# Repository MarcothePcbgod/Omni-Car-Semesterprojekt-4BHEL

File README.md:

# Omni-Car-Semesterprojekt-4BHEL
Backup für KiCad

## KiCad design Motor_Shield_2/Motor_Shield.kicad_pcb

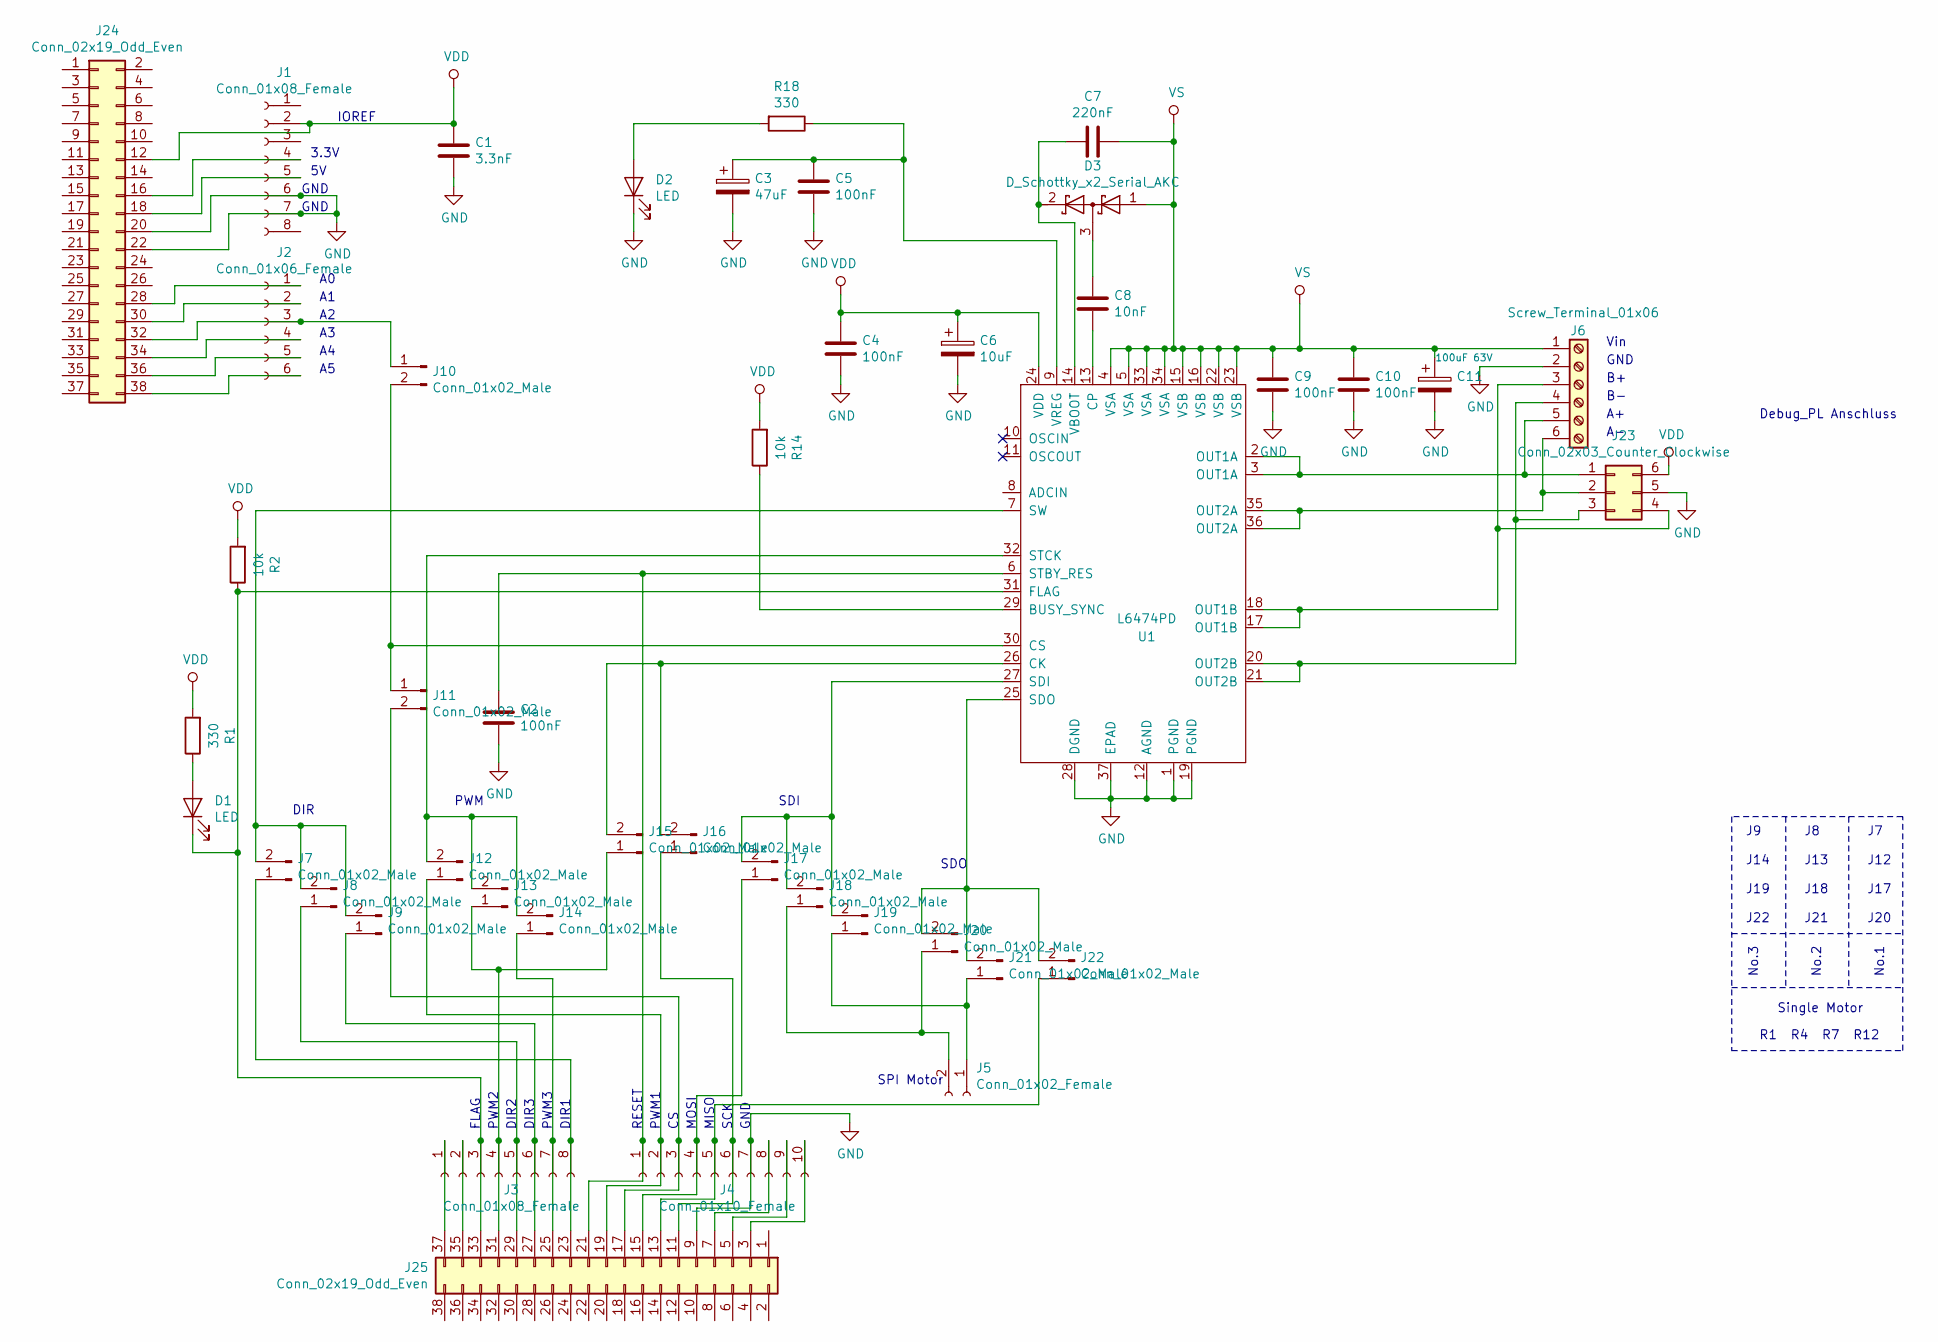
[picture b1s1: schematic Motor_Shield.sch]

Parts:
C1: 3.3nF; C_1206_3216Metric_Pad1.42x1.75mm_HandSolder
C2, C4, C5, C9, C10: 100nF; C_1206_3216Metric_Pad1.42x1.75mm_HandSolder
C3: 47uF; CP_EIA-3528-12_Kemet-T_Pad1.50x2.35mm_HandSolder
C6: 10uF; CP_EIA-3528-12_Kemet-T_Pad1.50x2.35mm_HandSolder
C7: 220nF; C_1206_3216Metric_Pad1.42x1.75mm_HandSolder
C8: 10nF; C_1206_3216Metric_Pad1.42x1.75mm_HandSolder
C11: 100uF 63V; C_Radial_D10.0mm_H20.0mm_P5.00mm
D1, D2: LED; D_1206_3216Metric_Pad1.42x1.75mm_HandSolder
D3: D_Schottky_x2_Serial_AKC; SC-59_Handsoldering
J1, J3: Conn_01x08_Female; PinSocket_1x08_P2.54mm_Vertical
J2: Conn_01x06_Female; PinSocket_1x06_P2.54mm_Vertical
J4: Conn_01x10_Female; PinSocket_1x10_P2.54mm_Vertical
J5: Conn_01x02_Female; PinSocket_1x02_P2.54mm_Vertical
J6: Screw_Terminal_01x06; TerminalBlock_bornier-6_P5.08mm
J7, J8, J9, J10, J11, J12, J13, J14, J15, J16, J17, J18, J19, J20, J21, J22: Conn_01x02_Male; PinHeader_1x02_P2.54mm_Vertical
J23: Conn_02x03_Counter_Clockwise; PinHeader_2x03_P2.54mm_Vertical
J24, J25: Conn_02x19_Odd_Even; PinHeader_2x19_P2.54mm_Vertical
R1, R18: 330; R_1206_3216Metric_Pad1.42x1.75mm_HandSolder
R2, R14: 10k; R_1206_3216Metric_Pad1.42x1.75mm_HandSolder
U1: L6474PD; ST_PowerSSO-36_SlugDown_ThermalVias

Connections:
GND: C1.2, C2.2, C3.2, C4.2, C5.2, C6.2, C9.2, C10.2, C11.2, D2.1 (K), J1.6, J1.7, J4.7, J6.2, J23.5, J24.20, J24.22, J25.9, U1.1 (PGND), U1.12 (AGND), U1.19 (PGND), U1.28 (DGND), U1.37 (EPAD)
unnamed: C2.1, J4.1, J25.21, U1.6 (STBY_RES)
unnamed: C3.1, C5.1, R18.1, U1.9 (VREG)
unnamed: C7.2, D3.2 (K), U1.14 (VBOOT)
unnamed: C8.1, D3.3 (common)
unnamed: C8.2, U1.13 (CP)
unnamed: D1.1 (K), J3.3, J25.33, R2.1, U1.31 (FLAG)
unnamed: D1.2 (A), R1.1
unnamed: D2.2 (A), R18.2
unnamed: J1.4, J24.16
unnamed: J1.5, J24.18
unnamed: J2.1, J24.28
unnamed: J2.2, J24.30
unnamed: J2.4, J24.34
unnamed: J2.5, J24.36
unnamed: J2.6, J24.38
unnamed: J7.2, J8.2, J9.2, U1.7 (SW)
unnamed: J2.3, J10.1, J24.32
unnamed: J10.2, J11.1, U1.30 (CS)
unnamed: J4.3, J11.2, J25.17
unnamed: J4.2, J12.1, J25.19
unnamed: J12.2, J13.2, J14.2, U1.32 (STCK)
unnamed: J3.4, J13.1, J15.1, J25.31
unnamed: J3.7, J14.1, J25.25
unnamed: J15.2, J16.2, U1.26 (CK)
unnamed: J4.6, J16.1, J25.11
unnamed: J4.4, J17.1, J25.15
unnamed: J17.2, J18.2, J19.2, U1.27 (SDI)
unnamed: J5.2, J18.1, J20.1
unnamed: J5.1, J19.1, J21.1
unnamed: J20.2, J21.2, J22.2, U1.25 (SDO)
unnamed: J4.5, J22.1, J25.13
unnamed: J6.5, J23.1, U1.2 (OUT1A), U1.3 (OUT1A)
unnamed: J6.6, J23.2, U1.35 (OUT2A), U1.36 (OUT2A)
unnamed: J6.4, J23.3, U1.20 (OUT2B), U1.21 (OUT2B)
unnamed: J6.3, J23.4, U1.17 (OUT1B), U1.18 (OUT1B)
unnamed: J4.10, J25.3
unnamed: J4.9, J25.5
unnamed: J4.8, J25.7
unnamed: J3.8, J7.1, J25.23
unnamed: J3.6, J9.1, J25.27
unnamed: J3.5, J8.1, J25.29
unnamed: J3.2, J25.35
unnamed: J3.1, J25.37
unnamed: R14.1, U1.29 (BUSY_SYNC)
VDD: C1.1, C4.1, C6.1, J1.2, J23.6, J24.12, R1.2, R2.2, R14.2, U1.24 (VDD)
VS: C7.1, C9.1, C10.1, C11.1, D3.1 (A), J6.1, U1.4 (VSA), U1.5 (VSA), U1.15 (VSB), U1.16 (VSB), U1.22 (VSB), U1.23 (VSB), U1.33 (VSA), U1.34 (VSA)

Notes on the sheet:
DIR
PWM
SDI
SDO
SPI Motor
No.3
No.2
No.1
Single Motor
R1 R4 R7 R12
Vin
GND
IOREF
3.3V
FLAG
PWM2
DIR2
DIR3
PWM3
DIR1
RESET
PWM1
MOSI
MISO
SCK
Debug_PL Anschluss
J7 J12 J17 J20
J8 J13 J18 J21
J9 J14 J19 J22

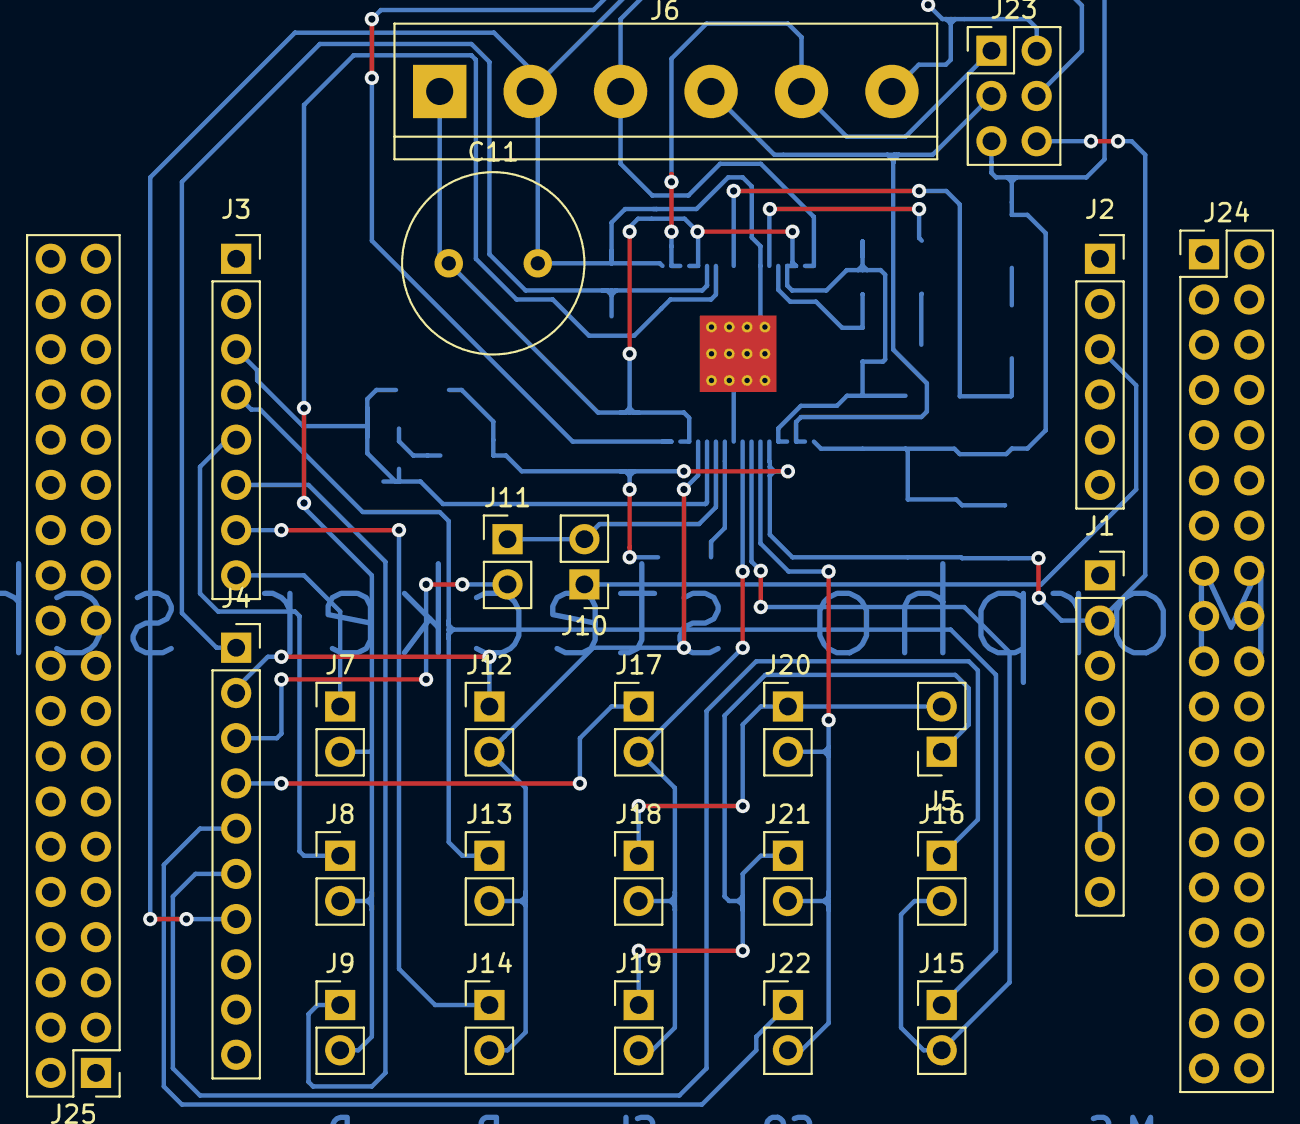
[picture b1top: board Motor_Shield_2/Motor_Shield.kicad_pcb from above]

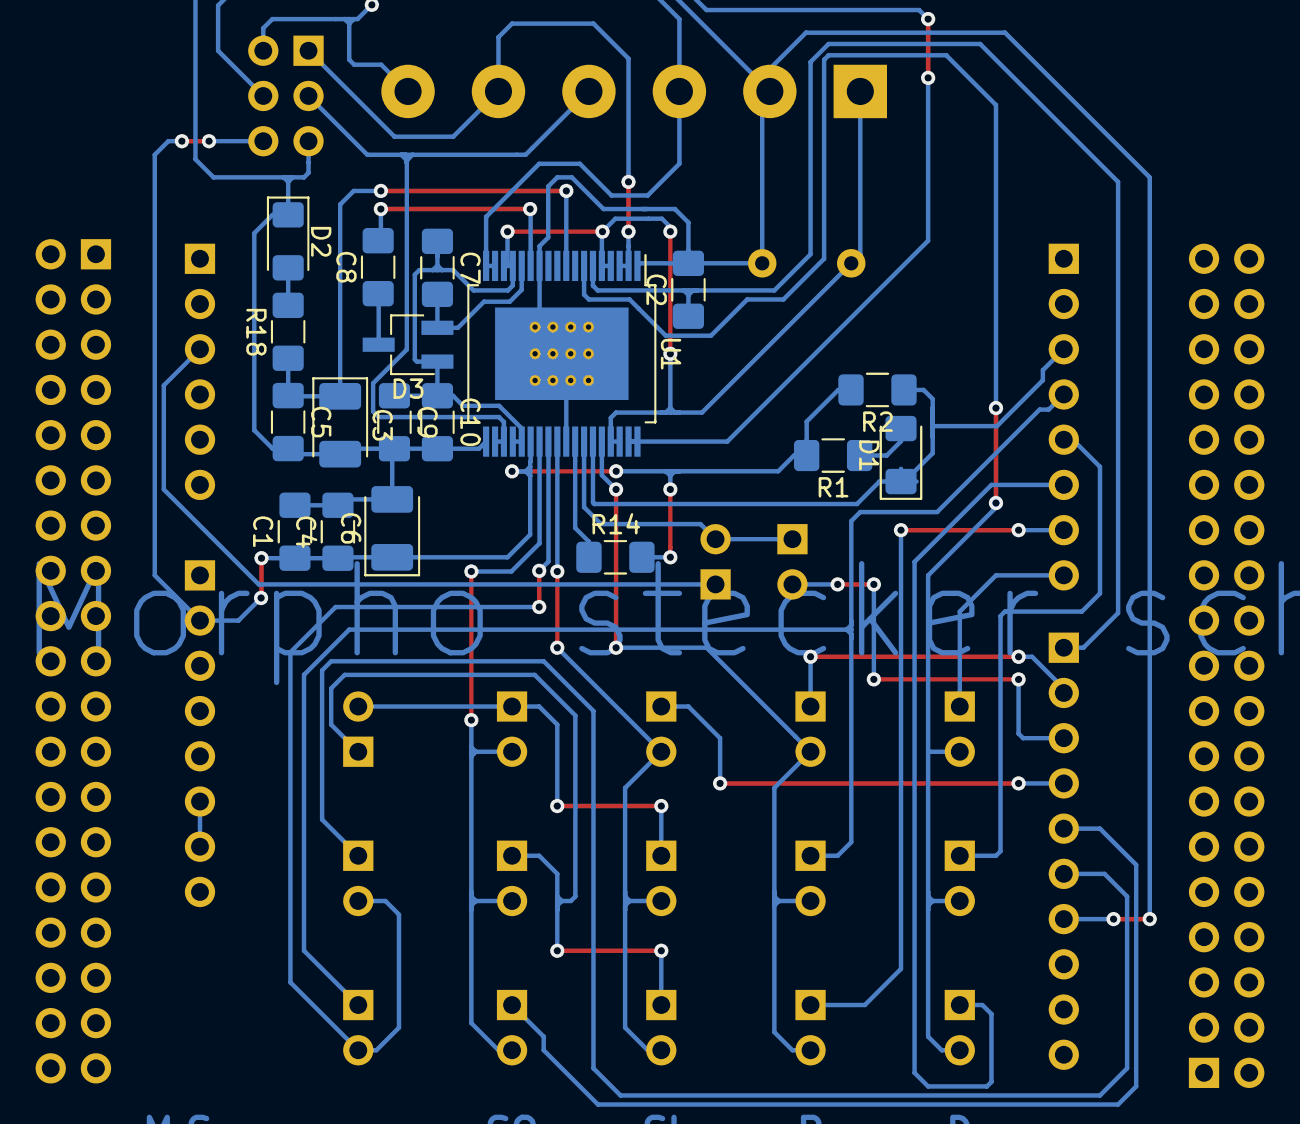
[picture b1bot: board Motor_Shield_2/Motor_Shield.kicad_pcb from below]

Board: 2 copper layers, 44 parts (18 on the bottom side), 47 nets.

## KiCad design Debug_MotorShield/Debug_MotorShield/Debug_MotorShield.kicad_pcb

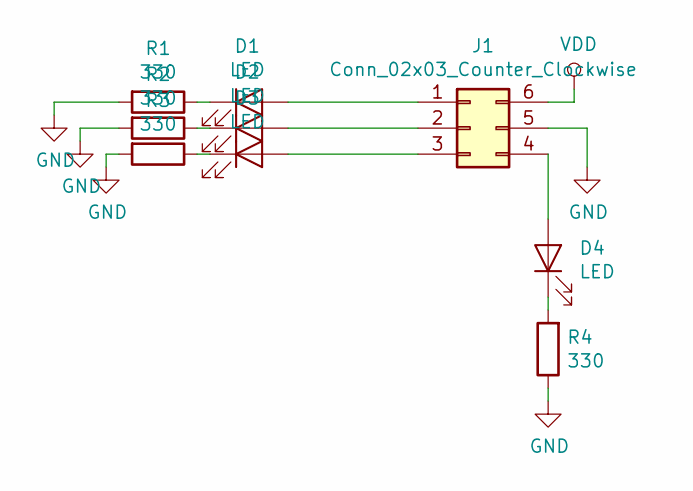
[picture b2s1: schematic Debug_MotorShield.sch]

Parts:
D1, D2, D3, D4: LED; LED_1206_3216Metric_Pad1.42x1.75mm_HandSolder
J1: Conn_02x03_Counter_Clockwise; PinHeader_2x03_P2.54mm_Vertical
R1, R2, R3, R4: 330; R_1206_3216Metric_Pad1.42x1.75mm_HandSolder

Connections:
GND: J1.5, R1.2, R2.2, R3.2, R4.1
unnamed: D1.1 (K), R1.1
unnamed: D1.2 (A), J1.1
unnamed: D2.1 (K), R2.1
unnamed: D2.2 (A), J1.2
unnamed: D3.1 (K), R3.1
unnamed: D3.2 (A), J1.3
unnamed: D4.1 (K), R4.2
unnamed: D4.2 (A), J1.4
VDD: J1.6

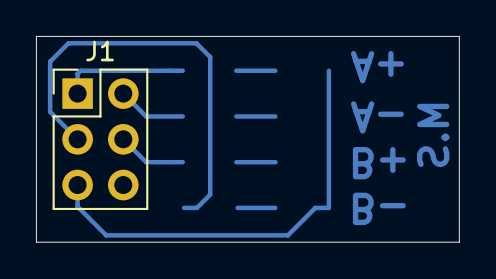
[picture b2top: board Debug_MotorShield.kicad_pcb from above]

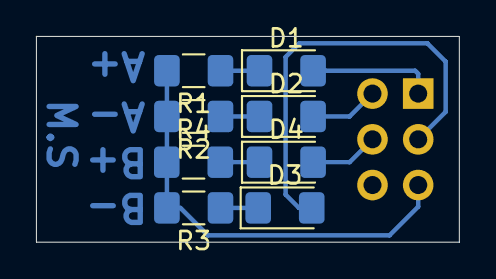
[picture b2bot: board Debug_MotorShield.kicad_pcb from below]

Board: 2 copper layers, 23.5 x 11.4 mm, 9 parts (8 on the bottom side), 9 nets.

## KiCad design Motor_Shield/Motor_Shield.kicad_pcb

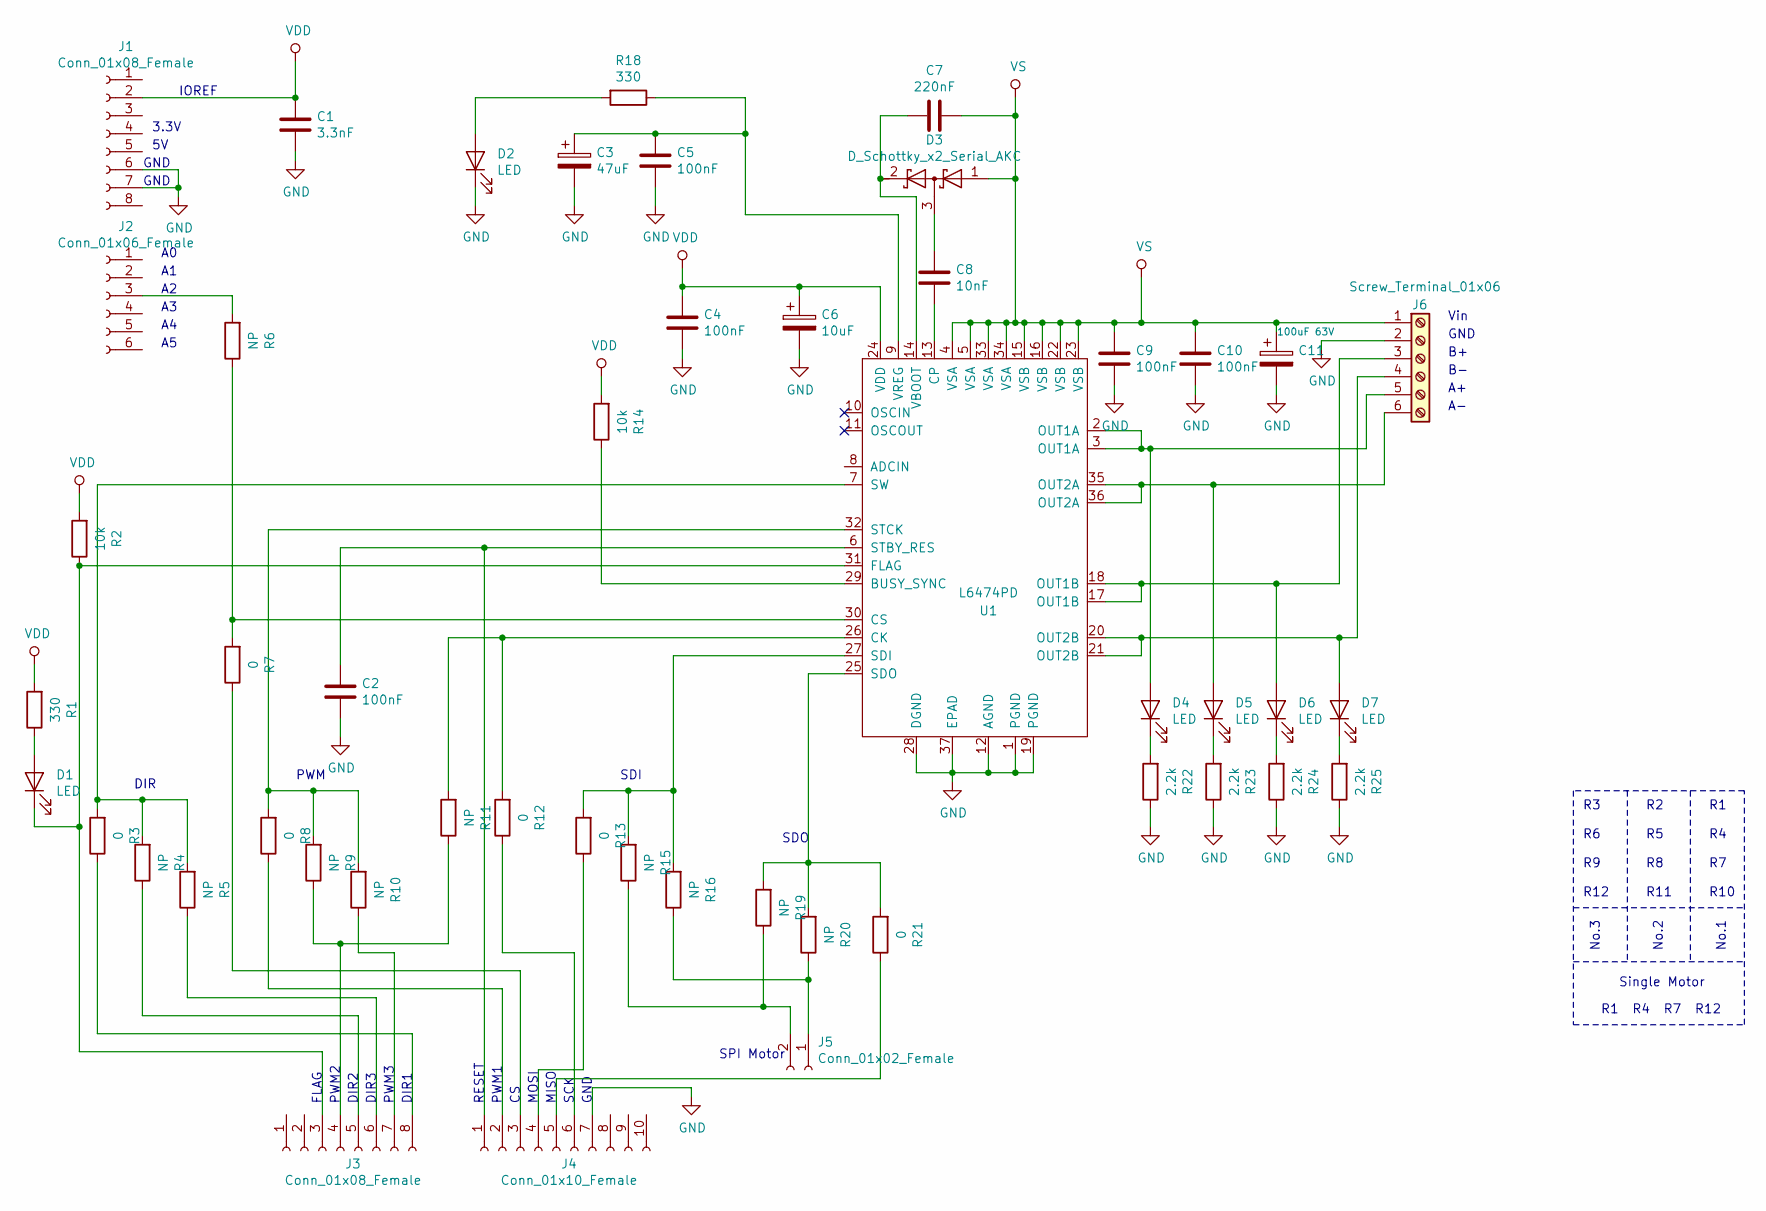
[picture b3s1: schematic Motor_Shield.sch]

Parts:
C1: 3.3nF; C_1206_3216Metric_Pad1.42x1.75mm_HandSolder
C2, C4, C5, C9, C10: 100nF; C_1206_3216Metric_Pad1.42x1.75mm_HandSolder
C3: 47uF; CP_EIA-3528-12_Kemet-T_Pad1.50x2.35mm_HandSolder
C6: 10uF; CP_EIA-3528-12_Kemet-T_Pad1.50x2.35mm_HandSolder
C7: 220nF; C_1206_3216Metric_Pad1.42x1.75mm_HandSolder
C8: 10nF; C_1206_3216Metric_Pad1.42x1.75mm_HandSolder
C11: 100uF 63V; C_Radial_D10.0mm_H20.0mm_P5.00mm
D1, D2: LED; D_1206_3216Metric_Pad1.42x1.75mm_HandSolder
D3: D_Schottky_x2_Serial_AKC; SC-59_Handsoldering
D4, D5, D6, D7: LED; D_1206_3216Metric
J1, J3: Conn_01x08_Female; PinSocket_1x08_P2.54mm_Vertical
J2: Conn_01x06_Female; PinSocket_1x06_P2.54mm_Vertical
J4: Conn_01x10_Female; PinSocket_1x10_P2.54mm_Vertical
J5: Conn_01x02_Female; PinSocket_1x02_P2.54mm_Vertical
J6: Screw_Terminal_01x06; TerminalBlock_bornier-6_P5.08mm
R1, R18: 330; R_1206_3216Metric_Pad1.42x1.75mm_HandSolder
R2, R14: 10k; R_1206_3216Metric_Pad1.42x1.75mm_HandSolder
R3, R7, R8, R12, R13, R21: 0; R_1206_3216Metric_Pad1.42x1.75mm_HandSolder
R4, R5, R6, R9, R10, R11, R15, R16, R19, R20: NP; R_1206_3216Metric_Pad1.42x1.75mm_HandSolder
R22, R23, R24, R25: 2.2k; R_1206_3216Metric_Pad1.42x1.75mm_HandSolder
U1: L6474PD; ST_PowerSSO-36_SlugDown_ThermalVias

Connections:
GND: C1.2, C2.2, C3.2, C4.2, C5.2, C6.2, C9.2, C10.2, C11.2, D2.1 (K), J1.6, J1.7, J4.7, J6.2, R22.1, R23.1, R24.1, R25.1, U1.1 (PGND), U1.12 (AGND), U1.19 (PGND), U1.28 (DGND), U1.37 (EPAD)
unnamed: C2.1, J4.1, U1.6 (STBY_RES)
unnamed: C3.1, C5.1, R18.1, U1.9 (VREG)
unnamed: C7.2, D3.2 (K), U1.14 (VBOOT)
unnamed: C8.1, D3.3 (common)
unnamed: C8.2, U1.13 (CP)
unnamed: D1.1 (K), J3.3, R2.1, U1.31 (FLAG)
unnamed: D1.2 (A), R1.1
unnamed: D2.2 (A), R18.2
unnamed: D4.1 (K), R22.2
unnamed: D4.2 (A), J6.5, U1.2 (OUT1A), U1.3 (OUT1A)
unnamed: D5.1 (K), R23.2
unnamed: D5.2 (A), J6.6, U1.35 (OUT2A), U1.36 (OUT2A)
unnamed: D6.1 (K), R24.2
unnamed: D6.2 (A), J6.3, U1.17 (OUT1B), U1.18 (OUT1B)
unnamed: D7.1 (K), R25.2
unnamed: D7.2 (A), J6.4, U1.20 (OUT2B), U1.21 (OUT2B)
unnamed: J2.3, R6.2
unnamed: J3.4, R9.1, R11.1
unnamed: J3.5, R4.1
unnamed: J3.6, R5.1
unnamed: J3.7, R10.1
unnamed: J3.8, R3.1
unnamed: J4.2, R8.1
unnamed: J4.3, R7.1
unnamed: J4.4, R13.1
unnamed: J4.5, R21.1
unnamed: J4.6, R12.1
unnamed: J5.1, R16.1, R20.1
unnamed: J5.2, R15.1, R19.1
unnamed: R3.2, R4.2, R5.2, U1.7 (SW)
unnamed: R6.1, R7.2, U1.30 (CS)
unnamed: R8.2, R9.2, R10.2, U1.32 (STCK)
unnamed: R11.2, R12.2, U1.26 (CK)
unnamed: R13.2, R15.2, R16.2, U1.27 (SDI)
unnamed: R14.1, U1.29 (BUSY_SYNC)
unnamed: R19.2, R20.2, R21.2, U1.25 (SDO)
VDD: C1.1, C4.1, C6.1, J1.2, R1.2, R2.2, R14.2, U1.24 (VDD)
VS: C7.1, C9.1, C10.1, C11.1, D3.1 (A), J6.1, U1.4 (VSA), U1.5 (VSA), U1.15 (VSB), U1.16 (VSB), U1.22 (VSB), U1.23 (VSB), U1.33 (VSA), U1.34 (VSA)

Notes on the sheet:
DIR
PWM
SDI
SDO
SPI Motor
R3 R6 R9 R12
R2 R5 R8 R11
R1 R4 R7 R10
No.3
No.2
No.1
Single Motor
R1 R4 R7 R12
Vin
GND
IOREF
3.3V
FLAG
PWM2
DIR2
DIR3
PWM3
DIR1
RESET
PWM1
MOSI
MISO
SCK

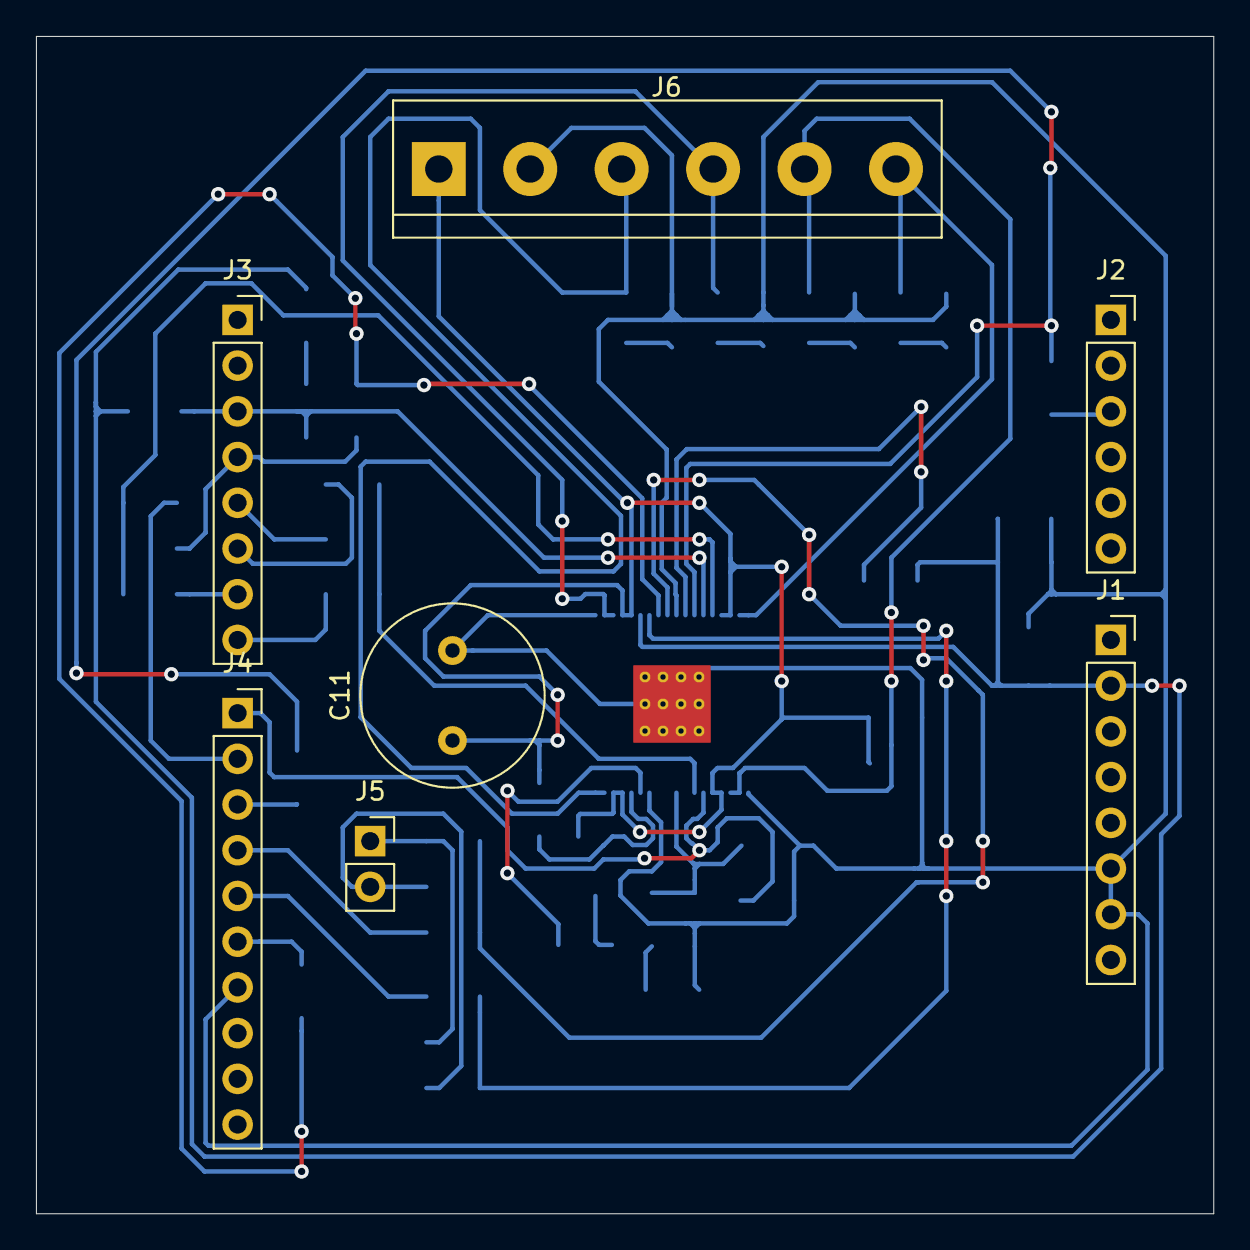
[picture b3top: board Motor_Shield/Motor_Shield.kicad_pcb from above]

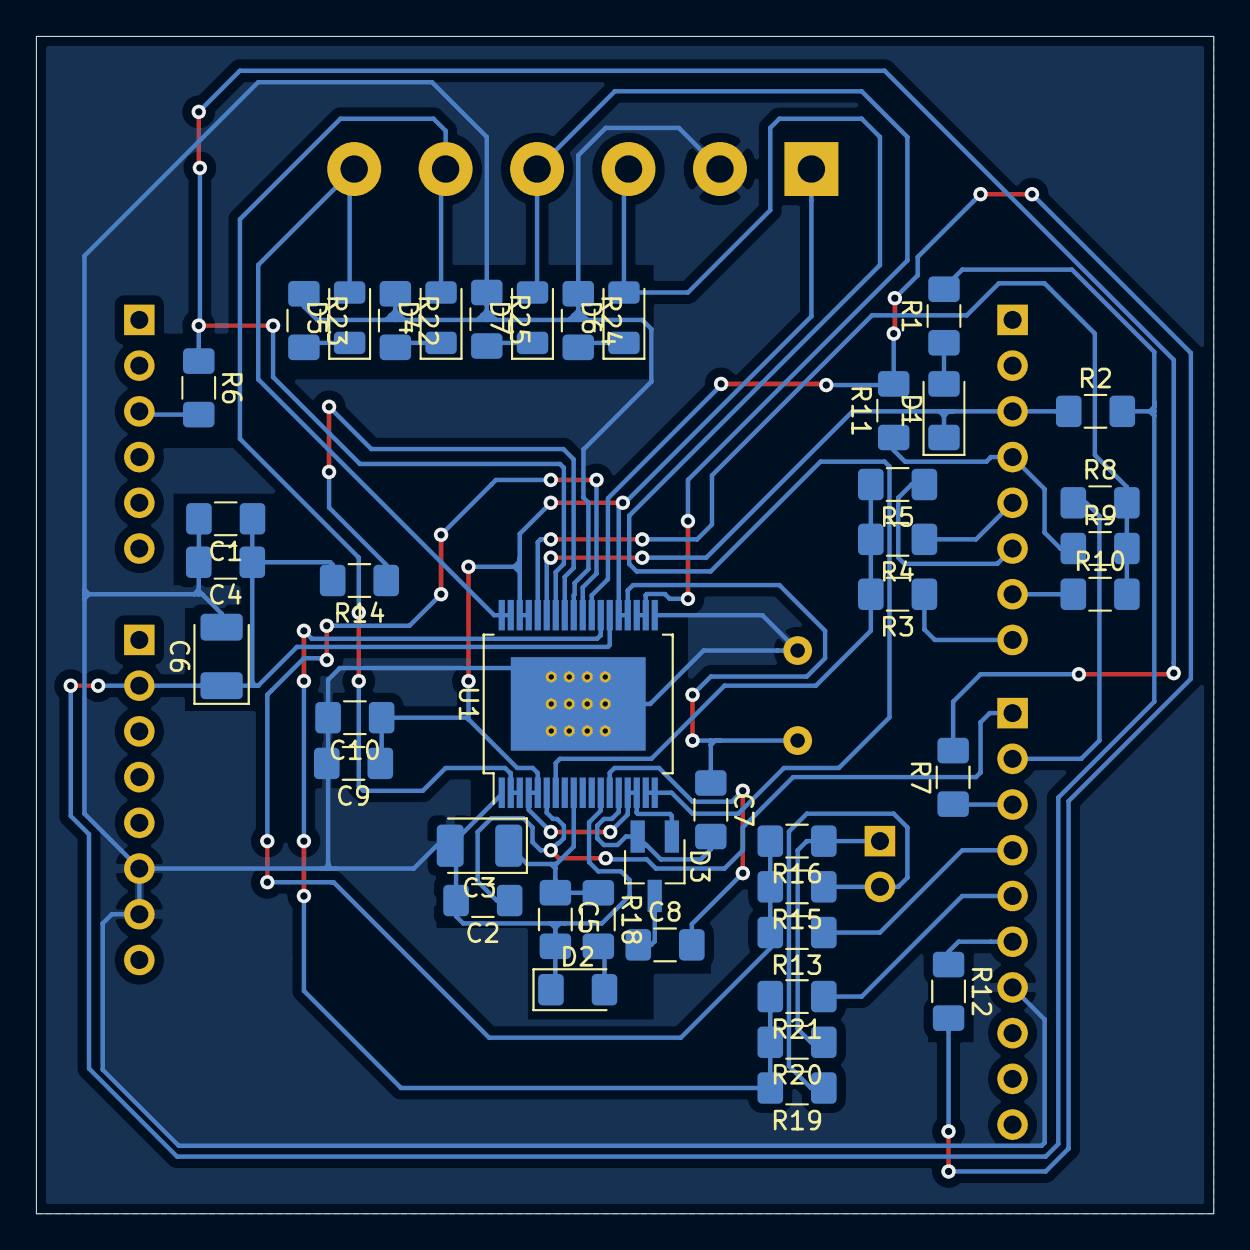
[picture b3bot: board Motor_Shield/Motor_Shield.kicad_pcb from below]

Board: 2 copper layers, 65.4 x 65.4 mm, 49 parts (42 on the bottom side), 39 nets.

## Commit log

2020-01-24 Erste Basis für AP und Datenübertragung
2020-01-24 Mögliche Bewegungen eingefügt
2020-01-25 Grid Def fehlt
2020-01-25 Array in HEX geändert
2020-01-25 Buttons richtig platziert
2020-01-26 Buttons entfernt und auf Keybindevents gendert
    N
2020-01-26 Buttons entfernt und auf Keybindevents geändert
    Nächster Schritt Darstellung von "Fakebuttons" mit Drückanimation
2020-01-27 TEST
2020-01-27 Buttonanimation hinzugefügt Optik fehlt
2020-01-27 Button sind jetzt Pfeile
2020-01-27 Ladebalken hinzugefügt
2020-01-28 Unnötige Buttons entfernt
2020-01-28 Unnötige Taskrequests wurden entfernt UNGETESTET
2020-01-28 Mögliche Funktion für Akkustatus
    Akkustatus Update ist drinnen aber nicht getestet weil send func im .ino file fehlt
2020-01-29 Auslesen der Webseite fertig verarbeitung fehlt
2020-01-29 Akkustand Req hinzugefügt
2020-01-29 Daten convert fertig
2020-01-31 PopUp-Fenster erstellt falls keine Verbindung
2020-02-02 First Blink Test
2020-02-16 Verbindungsbestätigung hinzugefügt
2020-02-17 swaped 57 with 58
2020-02-17 Zurück geswaped
2020-02-17 Error gefixed
2020-02-17 Pfade geupdated
2020-02-27 PCB angefangen
2020-02-28 UART Komm implementiert
2020-02-28 UART implementiert im INT-Mode
2020-02-28 Pcb fertig aber noch nicht optimal
2020-03-01 Version mit Pin Header statt SMD R
2020-03-02 pcb 70% fertig
2020-03-02 Fertig
2020-03-03 Überarbeiten das Pin Header schlecht plaziert waren
2020-03-03 PCB fertig
2020-03-03 Debug MotorShield fertig
2020-03-06 Morpho_Header hinzugefügt pcb fehlt aber noch
2020-06-13 mainC für Levelansteuerung
2020-06-13 Endbedinung hinzugefügt
2020-06-13 Levelshiftbefehlsverarbeitung
